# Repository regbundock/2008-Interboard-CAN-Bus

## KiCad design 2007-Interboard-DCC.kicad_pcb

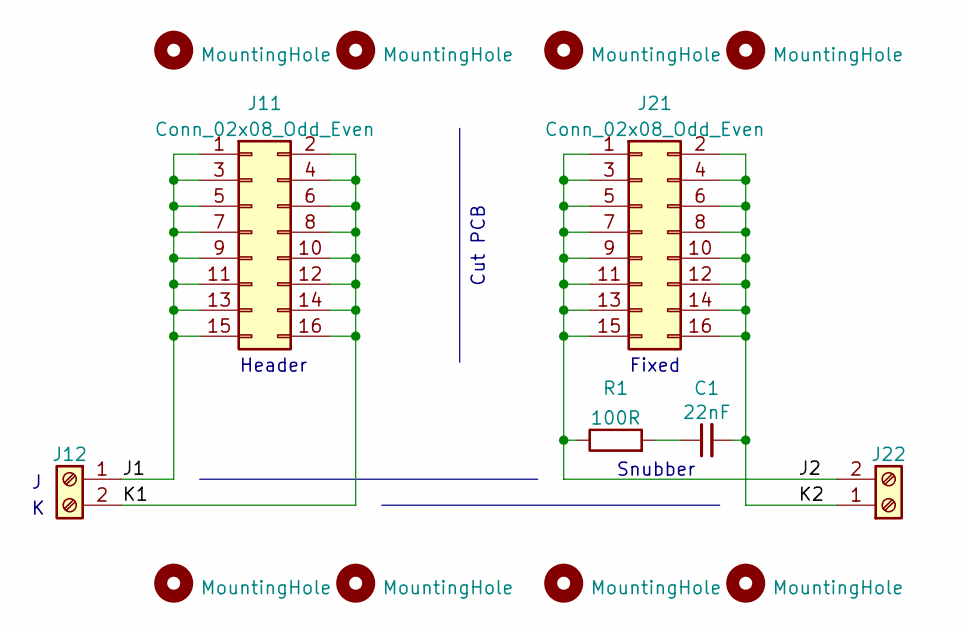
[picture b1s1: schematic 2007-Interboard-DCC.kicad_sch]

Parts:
C1: 22nF; C_Disc_D4.7mm_W2.5mm_P5.00mm
H1, H2, H3, H4, H5, H6, H7, H8: MountingHole; MountingHole_2.2mm_M2
J11: Conn_02x08_Odd_Even; IDC-Header_2x08_P2.54mm_Latch_Vertical
J12, J22: Screw_Terminal_01x02; Camdenboss_3pt5mm_pitch_PCB_horizontal_2Way
J21: Conn_02x08_Odd_Even; PinHeader_2x08_P2.54mm_Vertical
R1: 100R; R_Axial_P10.16mm_Horizontal

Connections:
/J1: J11.1, J11.3, J11.5, J11.7, J11.9, J11.11, J11.13, J11.15, J12.1
/J2: J21.1, J21.3, J21.5, J21.7, J21.9, J21.11, J21.13, J21.15, J22.2, R1.1
/K1: J11.2, J11.4, J11.6, J11.8, J11.10, J11.12, J11.14, J11.16, J12.2
/K2: C1.2, J21.2, J21.4, J21.6, J21.8, J21.10, J21.12, J21.14, J21.16, J22.1
unnamed: C1.1, R1.2

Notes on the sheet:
Header
Snubber
Cut PCB
Fixed

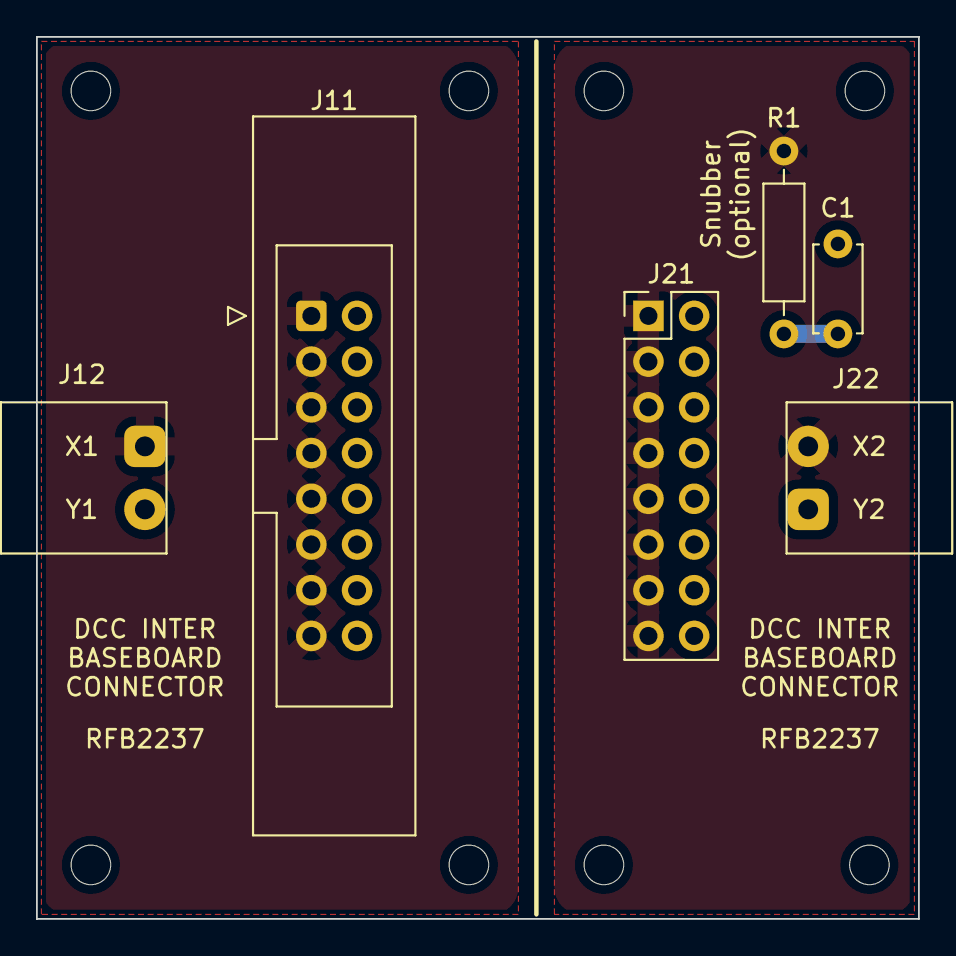
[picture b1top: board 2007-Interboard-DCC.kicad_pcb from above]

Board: 2 copper layers, 49.0 x 49.0 mm, 14 parts (0 on the bottom side), 5 nets.
